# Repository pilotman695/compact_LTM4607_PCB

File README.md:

# compact_LTM4607_PCB
A compact, 98% efficient, non-isolated DC-DC converter board based around the LTM4607

Input: 4.5-36V

Output: 0.8-24V, 5A (boost mode), 10A (buck mode)

## Version 1
Stand-off mounting, solderable wire connections

## Version 2
Card-edge style, compacted

Assembly tutorial: [https://www.youtube.com/watch?v=_QmpLCoHiIg](https://www.youtube.com/watch?v=_QmpLCoHiIg)

## Carrier Board
3 card-edge connectors, hotswapping, reverse polarity protection, switchable output nodes, undervoltage/overvoltage lockout

Input: 12.5-36V

Output: 3.3-24V

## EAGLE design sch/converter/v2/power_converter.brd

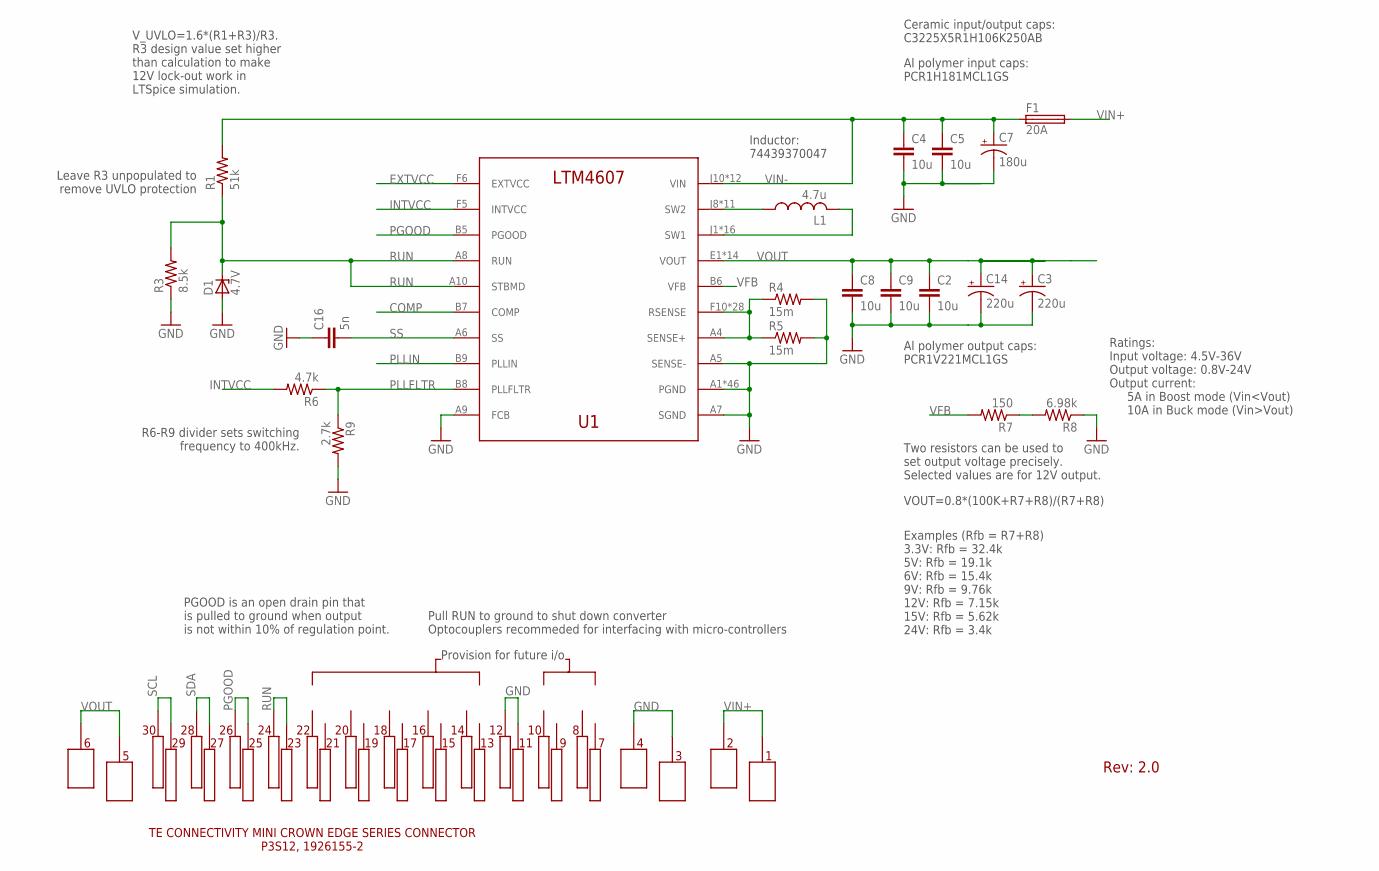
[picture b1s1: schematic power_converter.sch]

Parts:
C2, C4, C5, C8, C9: 10u; C1210
C3, C14: 220u; PCR1V221MCL1GS
C7: 180u; PCR1H181MCL1GS
C16: 5n; C0603
D1: 4.7V; SOD80C
F1: 20A; R1206
L1: 4.7u; PA4343.472ANLT
R1: 51k; R0603
R3: 8.5k; R0603
R4, R5: 15m; R1206
R6: 4.7k; R0603
R7: 150; R0603
R8: 6.98k; R0603
R9: 2.7k; R0603
U1: LTM4607EVPBF; LGA-141
U$1: 1926155-2_CARD

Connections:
COMP: U1.B7 (COMP)
EXTVCC: U1.F6 (EXTVCC)
GND: C2.2, C3.NEG (-), C4.2, C5.2, C7.NEG (-), C8.2, C9.2, C14.NEG (-), C16.1, D1.A, R3.1, R4.2, R5.2, R8.1, R9.2, U1.A1 (PGND), U1.A2 (PGND), U1.A3 (PGND), U1.A5 (SENSE-), U1.A7 (SGND), U1.A9 (FCB), U1.A11 (PGND), U1.A12 (PGND), U1.B1 (PGND), U1.B2 (PGND), U1.B3 (PGND), U1.B4 (PGND), U1.B10 (PGND), U1.B11 (PGND), U1.B12 (PGND), U1.C1 (PGND), U1.C2 (PGND), U1.C3 (PGND), U1.C4 (PGND), U1.C5 (PGND), U1.C6 (PGND), U1.C7 (PGND), U1.C8 (PGND), U1.C9 (PGND), U1.C10 (PGND), U1.C11 (PGND), U1.C12 (PGND), U1.D1 (PGND), U1.D2 (PGND), U1.D3 (PGND), U1.D4 (PGND), U1.D5 (PGND), U1.D6 (PGND), U1.D7 (PGND), U1.D8 (PGND), U1.D9 (PGND), U1.D10 (PGND), U1.D11 (PGND), U1.D12 (PGND), U1.E3 (PGND), U1.E4 (PGND), U1.E5 (PGND), U1.E6 (PGND), U1.E7 (PGND), U1.E8 (PGND), U1.E9 (PGND), U1.E10 (PGND), U1.E11 (PGND), U1.E12 (PGND), U$1.P$3, U$1.P$4, U$1.P$11, U$1.P$12
INTVCC: R6.2, U1.F5 (INTVCC)
unnamed: R7.1, R8.2
PGOOD: U1.B5 (PGOOD), U$1.P$25, U$1.P$26
PLLFLTR: R6.1, R9.1, U1.B8 (PLLFLTR)
PLLIN: U1.B9 (PLLIN)
RSENSE: R4.1, R5.1, U1.A4 (SENSE+), U1.F10 (RSENSE), U1.F11 (RSENSE), U1.F12 (RSENSE), U1.G5 (RSENSE), U1.G6 (RSENSE), U1.G7 (RSENSE), U1.G8 (RSENSE), U1.G9 (RSENSE), U1.G10 (RSENSE), U1.G11 (RSENSE), U1.G12 (RSENSE), U1.H5 (RSENSE), U1.H6 (RSENSE), U1.H7 (RSENSE), U1.H8 (RSENSE), U1.H9 (RSENSE), U1.H10 (RSENSE), U1.H11 (RSENSE), U1.H12 (RSENSE), U1.J5 (RSENSE), U1.J6 (RSENSE), U1.J7 (RSENSE), U1.K5 (RSENSE), U1.K6 (RSENSE), U1.L5 (RSENSE), U1.L6 (RSENSE), U1.M5 (RSENSE), U1.M6 (RSENSE)
RUN: D1.C, R1.1, R3.2, U1.A8 (RUN), U1.A10 (STBMD), U$1.P$23, U$1.P$24
SCL: U$1.P$29, U$1.P$30
SDA: U$1.P$27, U$1.P$28
SS: C16.2, U1.A6 (SS)
SW1: L1.P$2 (2), U1.J1 (SW1), U1.J2 (SW1), U1.J3 (SW1), U1.J4 (SW1), U1.K1 (SW1), U1.K2 (SW1), U1.K3 (SW1), U1.K4 (SW1), U1.L1 (SW1), U1.L2 (SW1), U1.L3 (SW1), U1.L4 (SW1), U1.M1 (SW1), U1.M2 (SW1), U1.M3 (SW1), U1.M4 (SW1)
SW2: L1.P$1 (1), U1.J8 (SW2), U1.J9 (SW2), U1.K7 (SW2), U1.K8 (SW2), U1.K9 (SW2), U1.L7 (SW2), U1.L8 (SW2), U1.L9 (SW2), U1.M7 (SW2), U1.M8 (SW2), U1.M9 (SW2)
VFB: R7.2, U1.B6 (VFB)
VIN+: F1.2, U$1.P$1, U$1.P$2
VIN-: C4.1, C5.1, C7.POS (+), F1.1, R1.2, U1.J10 (VIN), U1.J11 (VIN), U1.J12 (VIN), U1.K10 (VIN), U1.K11 (VIN), U1.K12 (VIN), U1.L10 (VIN), U1.L11 (VIN), U1.L12 (VIN), U1.M10 (VIN), U1.M11 (VIN), U1.M12 (VIN)
VOUT: C2.1, C3.POS (+), C8.1, C9.1, C14.POS (+), U1.E1 (VOUT), U1.E2 (VOUT), U1.F1 (VOUT), U1.F2 (VOUT), U1.F3 (VOUT), U1.F4 (VOUT), U1.G1 (VOUT), U1.G2 (VOUT), U1.G3 (VOUT), U1.G4 (VOUT), U1.H1 (VOUT), U1.H2 (VOUT), U1.H3 (VOUT), U1.H4 (VOUT), U$1.P$5, U$1.P$6

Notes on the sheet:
Ceramic input/output caps: C3225X5R1H106K250AB
Al polymer input caps: PCR1H181MCL1GS
Al polymer output caps: PCR1V221MCL1GS
Two resistors can be used to set output voltage precisely. Selected values are for 12V output.
VOUT=0.8*(100K+R7+R8)/(R7+R8)
V_UVLO=1.6*(R1+R3)/R3. R3 design value set higher than calculation to make 12V lock-out work in LTSpice simulation.
Leave R3 unpopulated to remove UVLO protection
R6-R9 divider sets switching frequency to 400kHz.
PGOOD is an open drain pin that is pulled to ground when output is not within 10% of regulation point.
Examples (Rfb = R7+R8) 3.3V: Rfb = 32.4k 5V: Rfb = 19.1k 6V: Rfb = 15.4k 9V: Rfb = 9.76k 12V: Rfb = 7.15k 15V: Rfb = 5.62k 24V: Rfb = 3.4k
Ratings: Input voltage: 4.5V-36V Output voltage: 0.8V-24V Output current: 5A in Boost mode (Vin<Vout) 10A in Buck mode (Vin>Vout)
Pull RUN to ground to shut down converter Optocouplers recommeded for interfacing with micro-controllers
Inductor: 74439370047
Rev: 2.0
Provision for future i/o

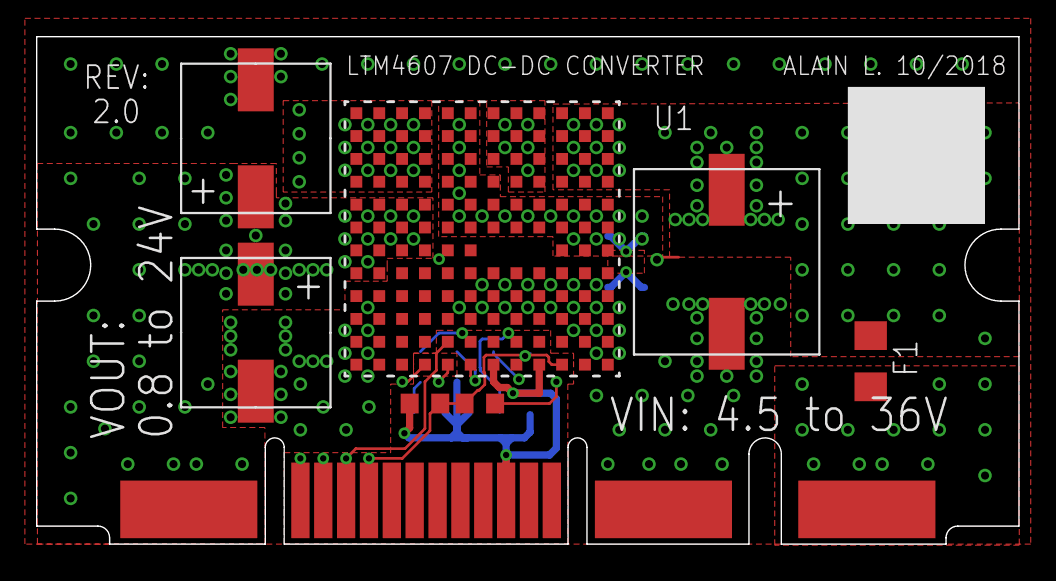
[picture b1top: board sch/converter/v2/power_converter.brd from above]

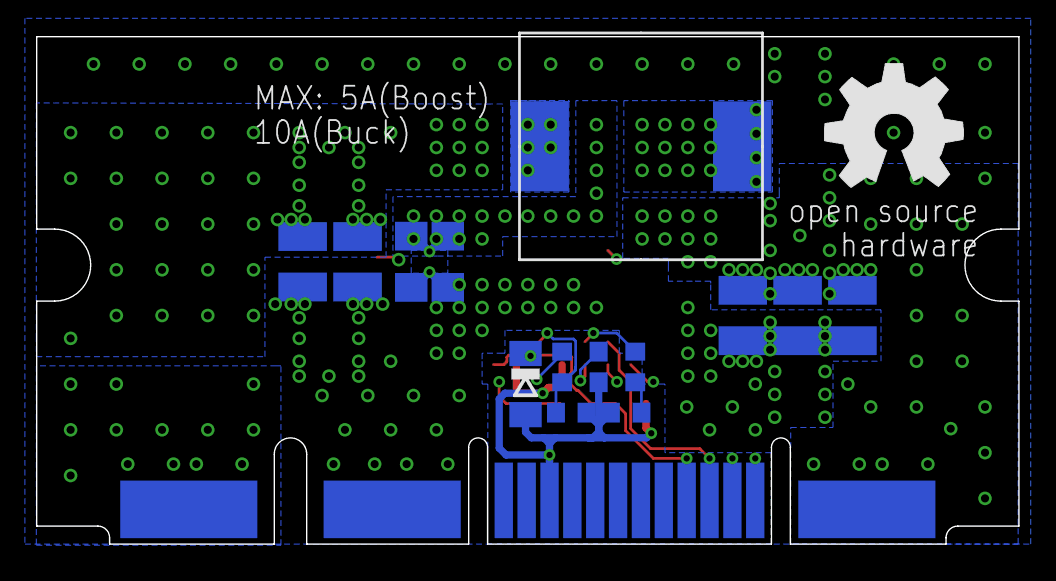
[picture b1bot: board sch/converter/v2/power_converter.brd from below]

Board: 4 copper layers, 54.6 x 28.2 mm, 24 parts (15 on the bottom side), 16 nets.

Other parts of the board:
U$2: OSHW_8MM
U$5: A4L-LOC

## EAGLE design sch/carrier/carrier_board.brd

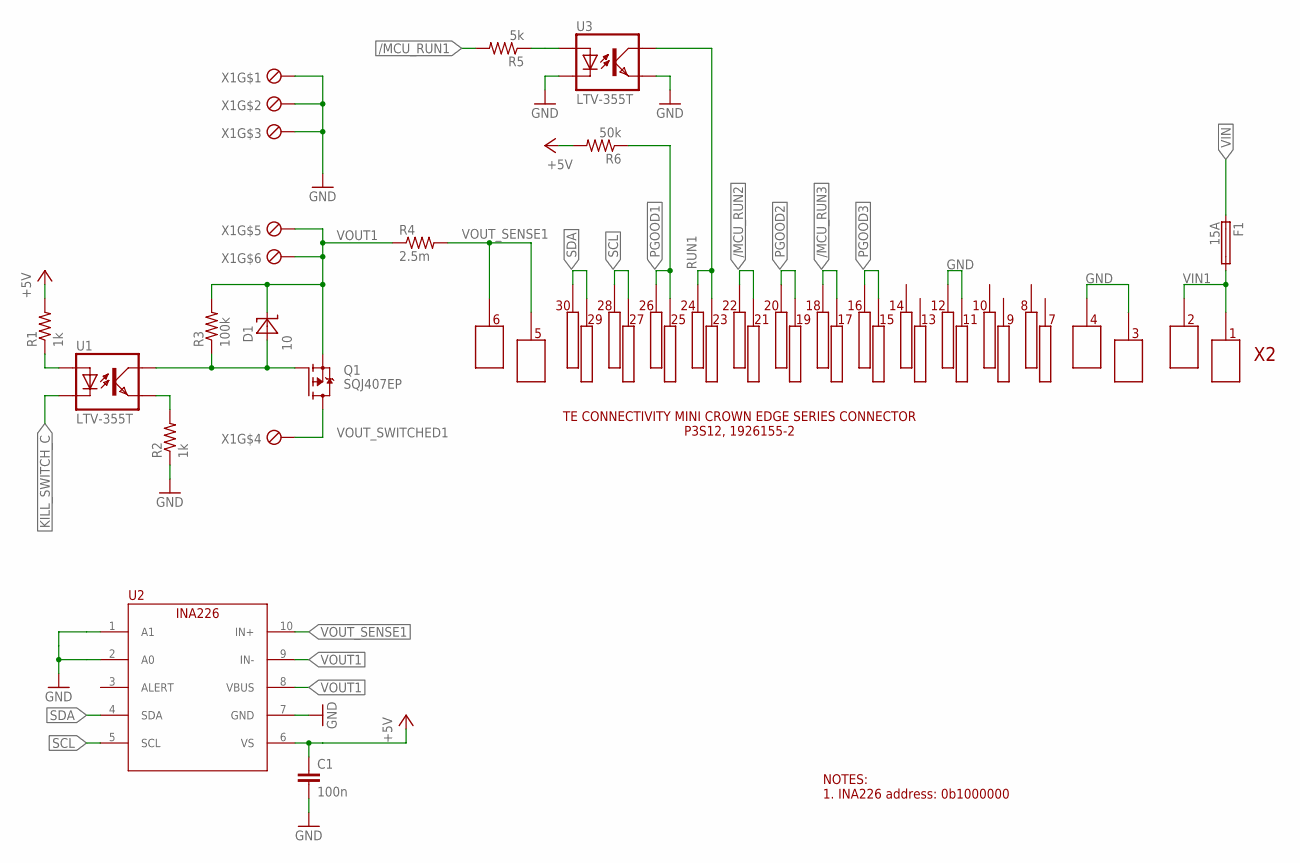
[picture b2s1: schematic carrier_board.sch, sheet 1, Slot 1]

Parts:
C1: 100n; C0603
D1: 10; SOD123
F1: 15A; 3557-10
Q1: SQJ407EP; POWERPAK_SO8L_SINGLE
R1, R2: 1k; R0603
R3: 100k; R0603
R4: 2.5m; R2512
R5: 5k; R0603
R6: 50k; R0603
U1, U3: LTV-355T; SMD4
U2: INA226; MSOP10
X1: 284391-6
X2: 1926155-2_SOCK

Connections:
+5V: C1.1, R1.2, R6.2, U2.6 (VS); also elsewhere on the board
/MCU_RUN1: R5.2; also elsewhere on the board
/MCU_RUN2: X2.P$21, X2.P$22; also elsewhere on the board
/MCU_RUN3: X2.P$17, X2.P$18; also elsewhere on the board
GATE_VOUT1: D1.2 (A), Q1.P$4 (G), R3.1, U1.COLLECTOR (COL)
GND: C1.2, R2.1, U2.1 (A1), U2.2 (A0), U2.7 (GND), U3.CATHODE (C), U3.EMITTER (EMIT), X1.P$1, X1.P$2, X1.P$3, X2.P$3_1, X2.P$3_2, X2.P$3_3, X2.P$4_1, X2.P$4_2, X2.P$4_3, X2.P$11, X2.P$12; also elsewhere on the board
KILL_SWITCH_C: U1.CATHODE (C); also elsewhere on the board
unnamed: R2.2, U1.EMITTER (EMIT)
unnamed: R5.1, U3.ANODE (A)
unnamed: R1.1, U1.ANODE (A)
PGOOD1: R6.1, X2.P$25, X2.P$26; also elsewhere on the board
PGOOD2: X2.P$19, X2.P$20; also elsewhere on the board
PGOOD3: X2.P$15, X2.P$16; also elsewhere on the board
RUN1: U3.COLLECTOR (COL), X2.P$23, X2.P$24
SCL: U2.5 (SCL), X2.P$27, X2.P$28; also elsewhere on the board
SDA: U2.4 (SDA), X2.P$29, X2.P$30; also elsewhere on the board
VIN: F1.P$1 (1), F1.P$2 (1); also elsewhere on the board
VIN1: F1.P$3 (2), F1.P$4 (2), X2.P$1_1, X2.P$1_2, X2.P$1_3, X2.P$2_1, X2.P$2_2, X2.P$2_3
VOUT1: D1.1 (C), Q1.P$1 (S), Q1.P$2 (S), Q1.P$3 (S), R3.2, R4.1, U2.8 (VBUS), U2.9 (IN-), X1.P$5, X1.P$6
VOUT_SENSE1: R4.2, U2.10 (IN+), X2.P$5_1, X2.P$5_2, X2.P$5_3, X2.P$6_1, X2.P$6_2, X2.P$6_3
VOUT_SWITCHED1: Q1.P$5 (D), Q1.P$6 (D), Q1.P$7 (D), Q1.P$8 (D), X1.P$4

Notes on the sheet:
NOTES: 1. INA226 address: 0b1000000

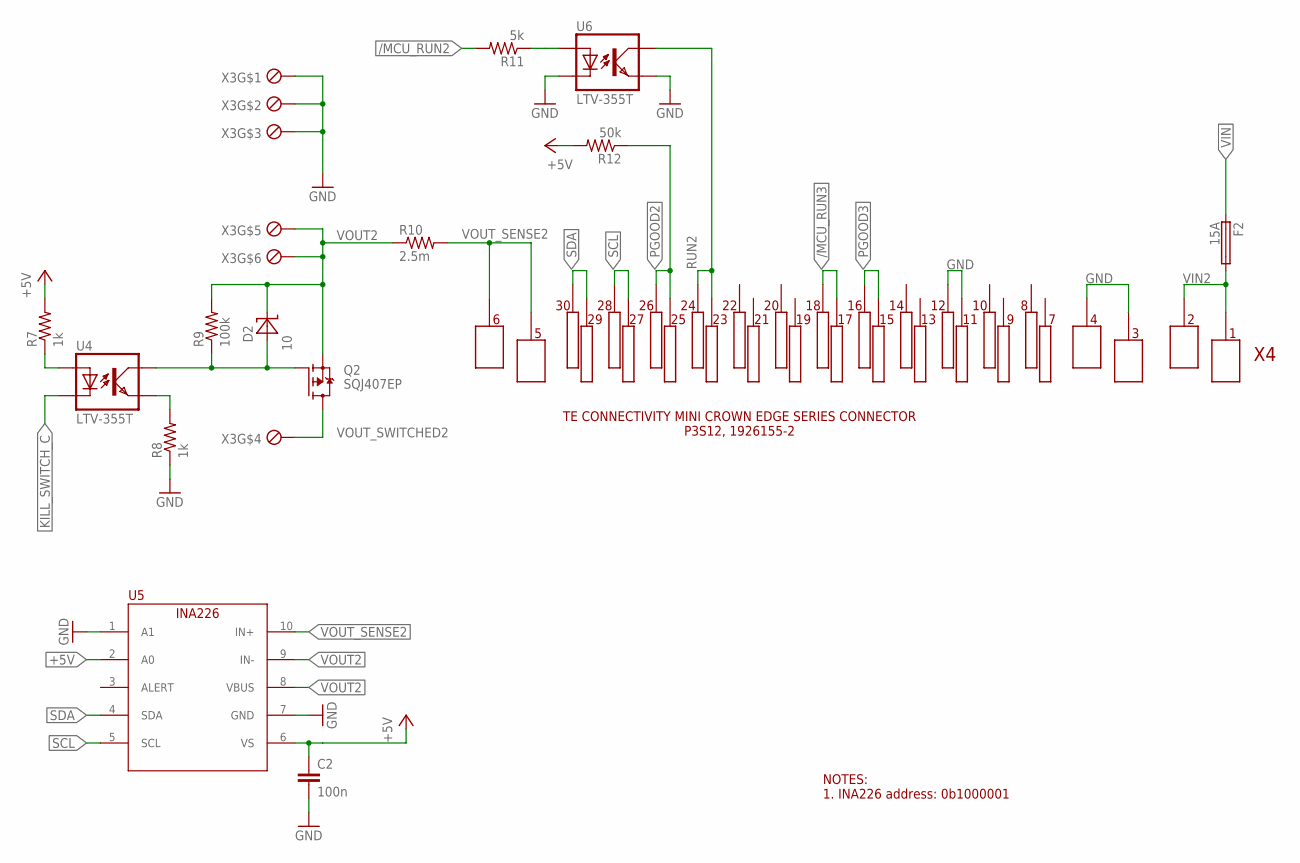
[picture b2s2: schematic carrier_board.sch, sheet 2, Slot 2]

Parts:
C2: 100n; C0603
D2: 10; SOD123
F2: 15A; 3557-10
Q2: SQJ407EP; POWERPAK_SO8L_SINGLE
R7, R8: 1k; R0603
R9: 100k; R0603
R10: 2.5m; R2512
R11: 5k; R0603
R12: 50k; R0603
U4, U6: LTV-355T; SMD4
U5: INA226; MSOP10
X3: 284391-6
X4: 1926155-2_SOCK

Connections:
+5V: C2.1, R7.2, R12.2, U5.2 (A0), U5.6 (VS); also elsewhere on the board
/MCU_RUN2: R11.2; also elsewhere on the board
/MCU_RUN3: X4.P$17, X4.P$18; also elsewhere on the board
GATE_VOUT2: D2.2 (A), Q2.P$4 (G), R9.1, U4.COLLECTOR (COL)
GND: C2.2, R8.1, U5.1 (A1), U5.7 (GND), U6.CATHODE (C), U6.EMITTER (EMIT), X3.P$1, X3.P$2, X3.P$3, X4.P$3_1, X4.P$3_2, X4.P$3_3, X4.P$4_1, X4.P$4_2, X4.P$4_3, X4.P$11, X4.P$12; also elsewhere on the board
KILL_SWITCH_C: U4.CATHODE (C); also elsewhere on the board
unnamed: R8.2, U4.EMITTER (EMIT)
unnamed: R7.1, U4.ANODE (A)
unnamed: R11.1, U6.ANODE (A)
PGOOD2: R12.1, X4.P$25, X4.P$26; also elsewhere on the board
PGOOD3: X4.P$15, X4.P$16; also elsewhere on the board
RUN2: U6.COLLECTOR (COL), X4.P$23, X4.P$24
SCL: U5.5 (SCL), X4.P$27, X4.P$28; also elsewhere on the board
SDA: U5.4 (SDA), X4.P$29, X4.P$30; also elsewhere on the board
VIN: F2.P$1 (1), F2.P$2 (1); also elsewhere on the board
VIN2: F2.P$3 (2), F2.P$4 (2), X4.P$1_1, X4.P$1_2, X4.P$1_3, X4.P$2_1, X4.P$2_2, X4.P$2_3
VOUT2: D2.1 (C), Q2.P$1 (S), Q2.P$2 (S), Q2.P$3 (S), R9.2, R10.1, U5.8 (VBUS), U5.9 (IN-), X3.P$5, X3.P$6
VOUT_SENSE2: R10.2, U5.10 (IN+), X4.P$5_1, X4.P$5_2, X4.P$5_3, X4.P$6_1, X4.P$6_2, X4.P$6_3
VOUT_SWITCHED2: Q2.P$5 (D), Q2.P$6 (D), Q2.P$7 (D), Q2.P$8 (D), X3.P$4

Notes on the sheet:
NOTES: 1. INA226 address: 0b1000001

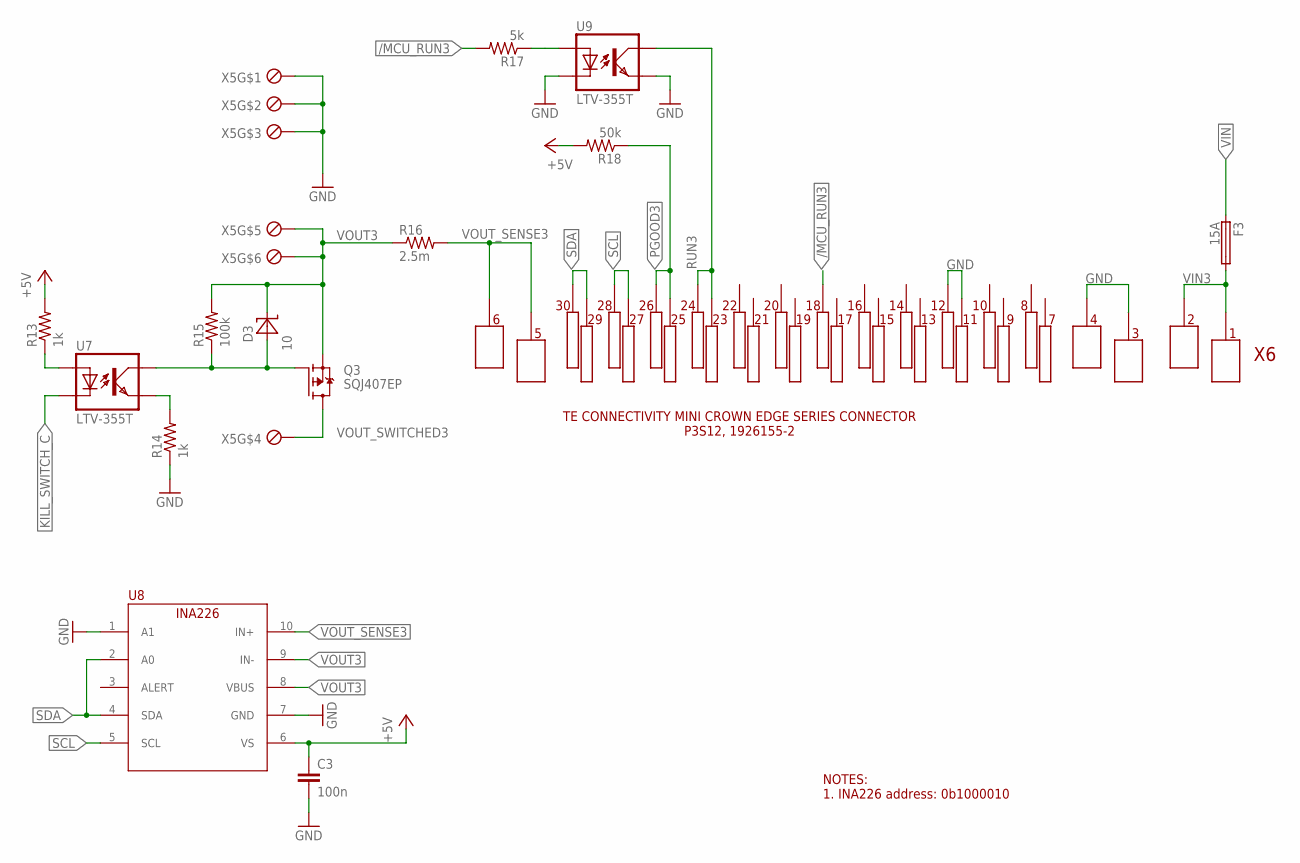
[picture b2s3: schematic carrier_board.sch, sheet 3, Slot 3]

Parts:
C3: 100n; C0603
D3: 10; SOD123
F3: 15A; 3557-10
Q3: SQJ407EP; POWERPAK_SO8L_SINGLE
R13, R14: 1k; R0603
R15: 100k; R0603
R16: 2.5m; R2512
R17: 5k; R0603
R18: 50k; R0603
U7, U9: LTV-355T; SMD4
U8: INA226; MSOP10
X5: 284391-6
X6: 1926155-2_SOCK

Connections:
+5V: C3.1, R13.2, R18.2, U8.6 (VS); also elsewhere on the board
/MCU_RUN3: R17.2, X6.P$18; also elsewhere on the board
GATE_VOUT3: D3.2 (A), Q3.P$4 (G), R15.1, U7.COLLECTOR (COL)
GND: C3.2, R14.1, U8.1 (A1), U8.7 (GND), U9.CATHODE (C), U9.EMITTER (EMIT), X5.P$1, X5.P$2, X5.P$3, X6.P$3_1, X6.P$3_2, X6.P$3_3, X6.P$4_1, X6.P$4_2, X6.P$4_3, X6.P$11, X6.P$12; also elsewhere on the board
KILL_SWITCH_C: U7.CATHODE (C); also elsewhere on the board
unnamed: R14.2, U7.EMITTER (EMIT)
unnamed: R13.1, U7.ANODE (A)
unnamed: R17.1, U9.ANODE (A)
PGOOD3: R18.1, X6.P$25, X6.P$26; also elsewhere on the board
RUN3: U9.COLLECTOR (COL), X6.P$23, X6.P$24
SCL: U8.5 (SCL), X6.P$27, X6.P$28; also elsewhere on the board
SDA: U8.2 (A0), U8.4 (SDA), X6.P$29, X6.P$30; also elsewhere on the board
VIN: F3.P$1 (1), F3.P$2 (1); also elsewhere on the board
VIN3: F3.P$3 (2), F3.P$4 (2), X6.P$1_1, X6.P$1_2, X6.P$1_3, X6.P$2_1, X6.P$2_2, X6.P$2_3
VOUT3: D3.1 (C), Q3.P$1 (S), Q3.P$2 (S), Q3.P$3 (S), R15.2, R16.1, U8.8 (VBUS), U8.9 (IN-), X5.P$5, X5.P$6
VOUT_SENSE3: R16.2, U8.10 (IN+), X6.P$5_1, X6.P$5_2, X6.P$5_3, X6.P$6_1, X6.P$6_2, X6.P$6_3
VOUT_SWITCHED3: Q3.P$5 (D), Q3.P$6 (D), Q3.P$7 (D), Q3.P$8 (D), X5.P$4

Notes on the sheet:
NOTES: 1. INA226 address: 0b1000010

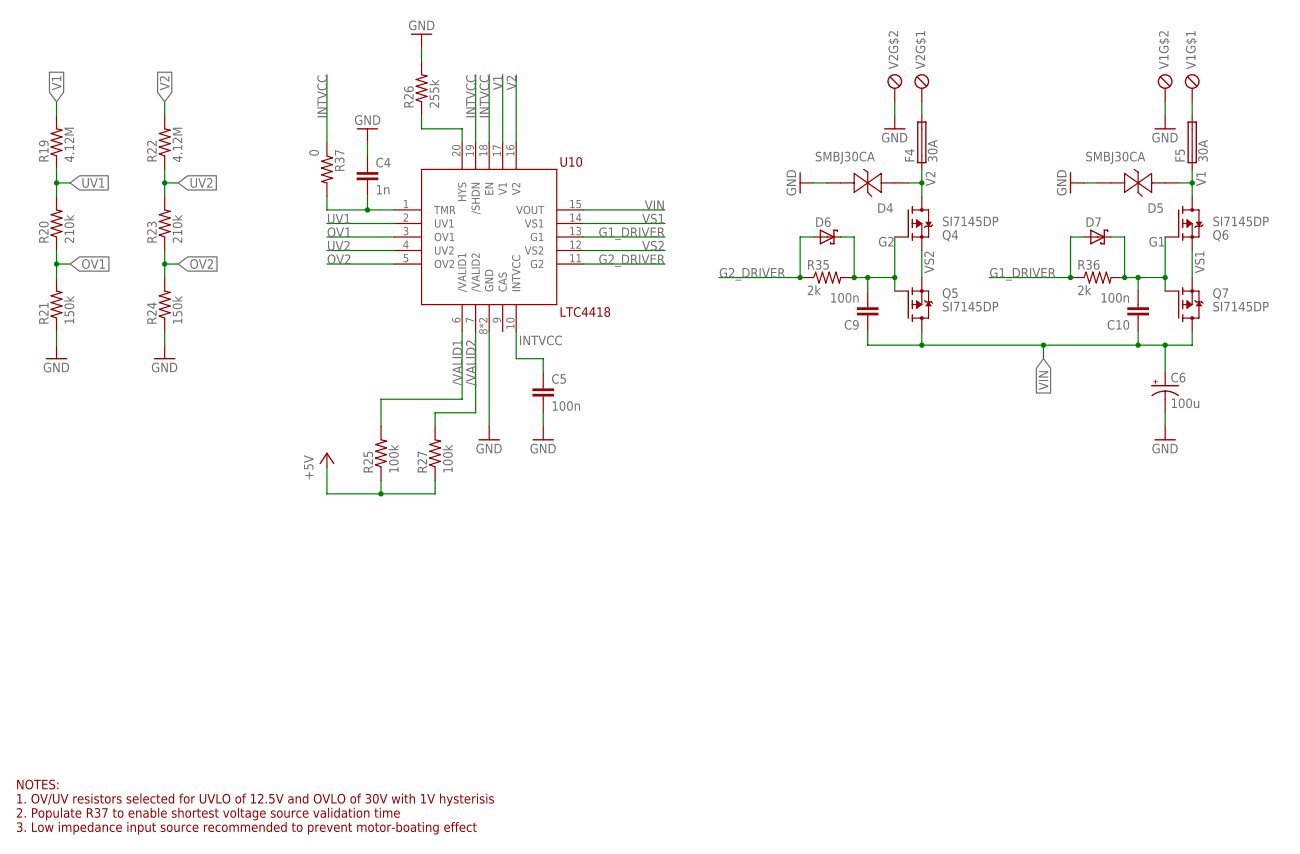
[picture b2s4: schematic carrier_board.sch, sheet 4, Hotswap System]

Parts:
C4: 1n; C0402
C5: 100n; C0402
C6: 100u; E5-10,5
C9, C10: 100n; C0603
D4, D5: SMBJ30CA; DO214AA
D6, D7: SD0603S040S0R2; CHIPLED_0603
F4, F5: 30A; 3557-10
Q4, Q5, Q6, Q7: SI7145DP; SO-8-POWERPAK
R19, R22: 4.12M; R0402
R20, R23: 210k; R0402
R21, R24: 150k; R0402
R25, R27: 100k; R0603
R26: 255k; R0402
R35, R36: 2k; R0603
R37: 0; R0402
U10: LTC4418; QFN20
V1, V2: MKDSD_1730502

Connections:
+5V: R25.1, R27.1; also elsewhere on the board
/VALID1: R25.2, U10.6 (/VALID1); also elsewhere on the board
/VALID2: R27.2, U10.7 (/VALID2); also elsewhere on the board
G1: C10.2, D7.C, Q6.4 (G), Q7.4 (G), R36.2
G1_DRIVER: D7.A, R36.1, U10.13 (G1)
G2: C9.2, D6.C, Q4.4 (G), Q5.4 (G), R35.2
G2_DRIVER: D6.A, R35.1, U10.11 (G2)
GND: C4.1, C5.2, C6.-, D4.A (2), D5.A (2), R21.1, R24.1, R26.2, U10.8 (GND), U10.EXP (GND), V1.P$2, V1.P$4, V2.P$2, V2.P$4; also elsewhere on the board
HYS: R26.1, U10.20 (HYS)
INTVCC: C5.1, R37.1, U10.10 (INTVCC), U10.18 (EN), U10.19 (/SHDN)
OV1: R20.1, R21.2, U10.3 (OV1)
OV2: R23.1, R24.2, U10.5 (OV2)
TMR: C4.2, R37.2, U10.1 (TMR)
UV1: R19.1, R20.2, U10.2 (UV1)
UV2: R22.1, R23.2, U10.4 (UV2)
V1: D5.C (1), F5.P$1 (1), F5.P$2 (1), Q6.5 (D), Q6.6 (D), Q6.7 (D), Q6.8 (D), Q6.P$1 (D), R19.2, U10.17 (V1)
V2: D4.C (1), F4.P$1 (1), F4.P$2 (1), Q4.5 (D), Q4.6 (D), Q4.7 (D), Q4.8 (D), Q4.P$1 (D), R22.2, U10.16 (V2)
VBAT1: F5.P$3 (2), F5.P$4 (2), V1.P$1, V1.P$3
VBAT2: F4.P$3 (2), F4.P$4 (2), V2.P$1, V2.P$3
VIN: C6.+, C9.1, C10.1, Q5.5 (D), Q5.6 (D), Q5.7 (D), Q5.8 (D), Q5.P$1 (D), Q7.5 (D), Q7.6 (D), Q7.7 (D), Q7.8 (D), Q7.P$1 (D), U10.15 (VOUT); also elsewhere on the board
VS1: Q6.1 (S), Q6.2 (S), Q6.3 (S), Q7.1 (S), Q7.2 (S), Q7.3 (S), U10.14 (VS1)
VS2: Q4.1 (S), Q4.2 (S), Q4.3 (S), Q5.1 (S), Q5.2 (S), Q5.3 (S), U10.12 (VS2)

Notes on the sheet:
NOTES: 1. OV/UV resistors selected for UVLO of 12.5V and OVLO of 30V with 1V hysterisis 2. Populate R37 to enable shortest voltage source validation time 3. Low impedance input source recommended to prevent motor-boating effect

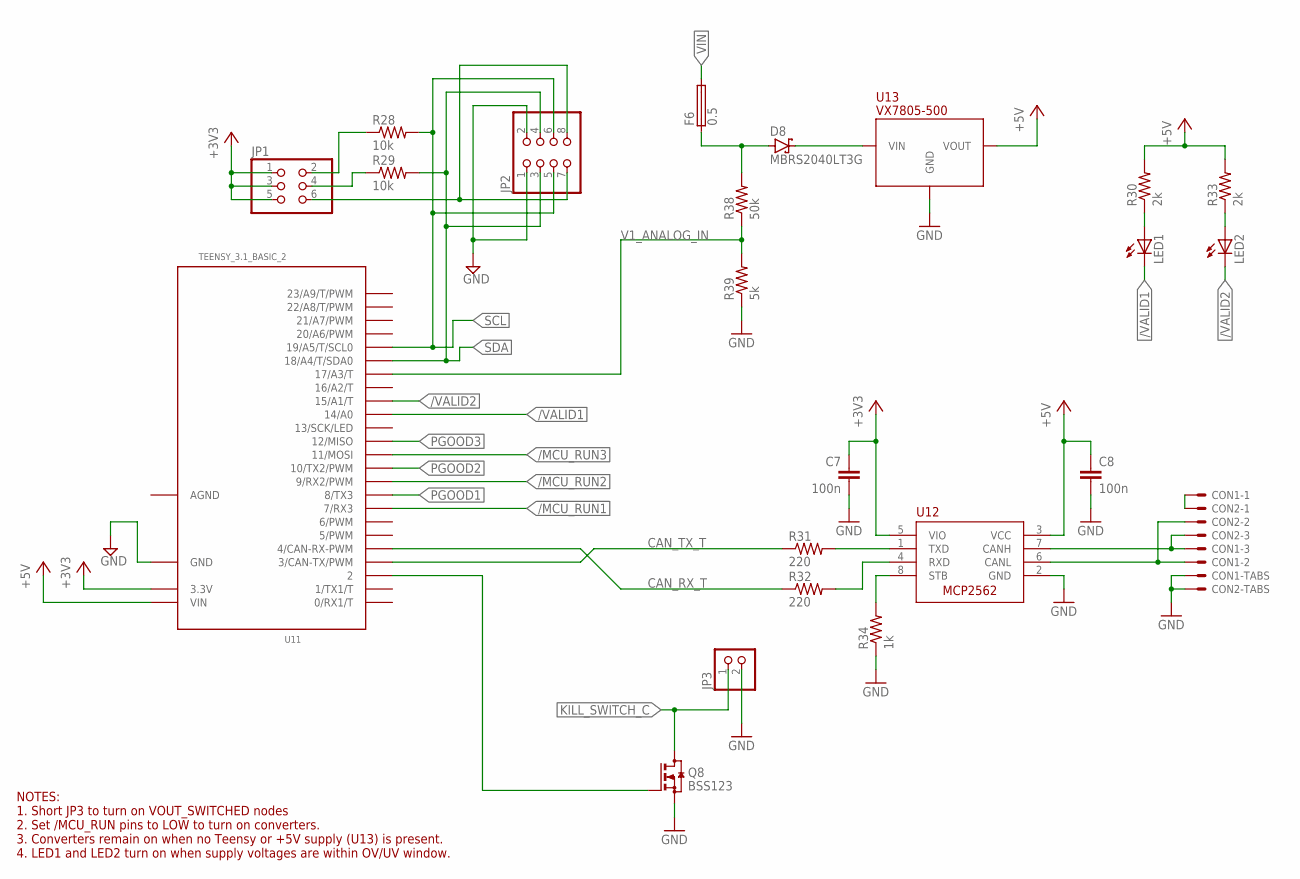
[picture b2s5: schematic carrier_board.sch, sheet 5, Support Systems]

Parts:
C7, C8: 100n; C0805
CON1, CON2: SM03B-GHS-TB
D8: MBRS2040LT3G; SMB
F6: 0.5; R1206
JP1: PINHD-2X3; 2X03
JP2: PINHD-2X4; 2X04
JP3: PINHD-1X02_2.54-SMD-90°; 1X02SMD/90
LED1, LED2: LEDCHIPLED_0603; CHIPLED_0603
Q8: BSS123; SOT23
R28, R29: 10k; R0805
R30, R33: 2k; R0603
R31, R32: 220; R0805
R34: 1k; R0805
R38: 50k; R0603
R39: 5k; R0603
U11: TEENSY_3.1_BASIC_2
U12: MCP2562; SO-8
U13: VX7805-500; 0.1"_LINEAR_REGULATOR_REPLACEMENT

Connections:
+3V3: C7.1, JP1.1, JP1.3, JP1.5, U11.3.3V, U12.5 (VIO)
+5V: C8.1, R30.2, R33.2, U11.VIN, U12.3 (VCC), U13.3 (VOUT); also elsewhere on the board
/MCU_RUN1: U11.7 (7/RX3); also elsewhere on the board
/MCU_RUN2: U11.9 (9/RX2/PWM); also elsewhere on the board
/MCU_RUN3: U11.11 (11/MOSI); also elsewhere on the board
/VALID1: LED1.C, U11.14/A0; also elsewhere on the board
/VALID2: LED2.C, U11.15/A1 (15/A1/T); also elsewhere on the board
AGND: U11.AGND
CANH: CON1.P$3, CON2.P$3, U12.7 (CANH)
CANL: CON1.P$2, CON2.P$2, U12.6 (CANL)
CANSH: CON1.P$1, CON2.P$1
CAN_RX: R32.2, U12.4 (RXD)
CAN_RX_T: R32.1, U11.4 (4/CAN-RX-PWM)
CAN_TX: R31.2, U12.1 (TXD)
CAN_TX_T: R31.1, U11.3 (3/CAN-TX/PWM)
GND: C7.2, C8.2, CON1.P$4, CON1.P$5, CON2.P$4, CON2.P$5, JP2.1, JP2.2, JP3.2, Q8.2 (S), R34.1, R39.1, U11.GND, U12.2 (GND), U13.2 (GND); also elsewhere on the board
I2C_3V3: JP1.6, JP2.7, JP2.8
KILL_SWITCH_C: JP3.1, Q8.3 (D); also elsewhere on the board
unnamed: D8.A, F6.1, R38.2
unnamed: LED1.A, R30.1
unnamed: LED2.A, R33.1
unnamed: Q8.1 (G), U11.2
unnamed: D8.C, U13.1 (VIN)
PGOOD1: U11.8 (8/TX3); also elsewhere on the board
PGOOD2: U11.10 (10/TX2/PWM); also elsewhere on the board
PGOOD3: U11.12 (12/MISO); also elsewhere on the board
SCL: JP2.5, JP2.6, R28.2, U11.19/A5 (19/A5/T/SCL0); also elsewhere on the board
SCL_3V3: JP1.2, R28.1
SDA: JP2.3, JP2.4, R29.2, U11.18/A4 (18/A4/T/SDA0); also elsewhere on the board
SDA_3V3: JP1.4, R29.1
STB: R34.2, U12.8 (STB)
V1_ANALOG_IN: R38.1, R39.2, U11.17/A3 (17/A3/T)
VIN: F6.2; also elsewhere on the board

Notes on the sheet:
NOTES: 1. Short JP3 to turn on VOUT_SWITCHED nodes 2. Set /MCU_RUN pins to LOW to turn on converters. 3. Converters remain on when no Teensy or +5V supply (U13) is present. 4. LED1 and LED2 turn on when supply voltages are within OV/UV window.

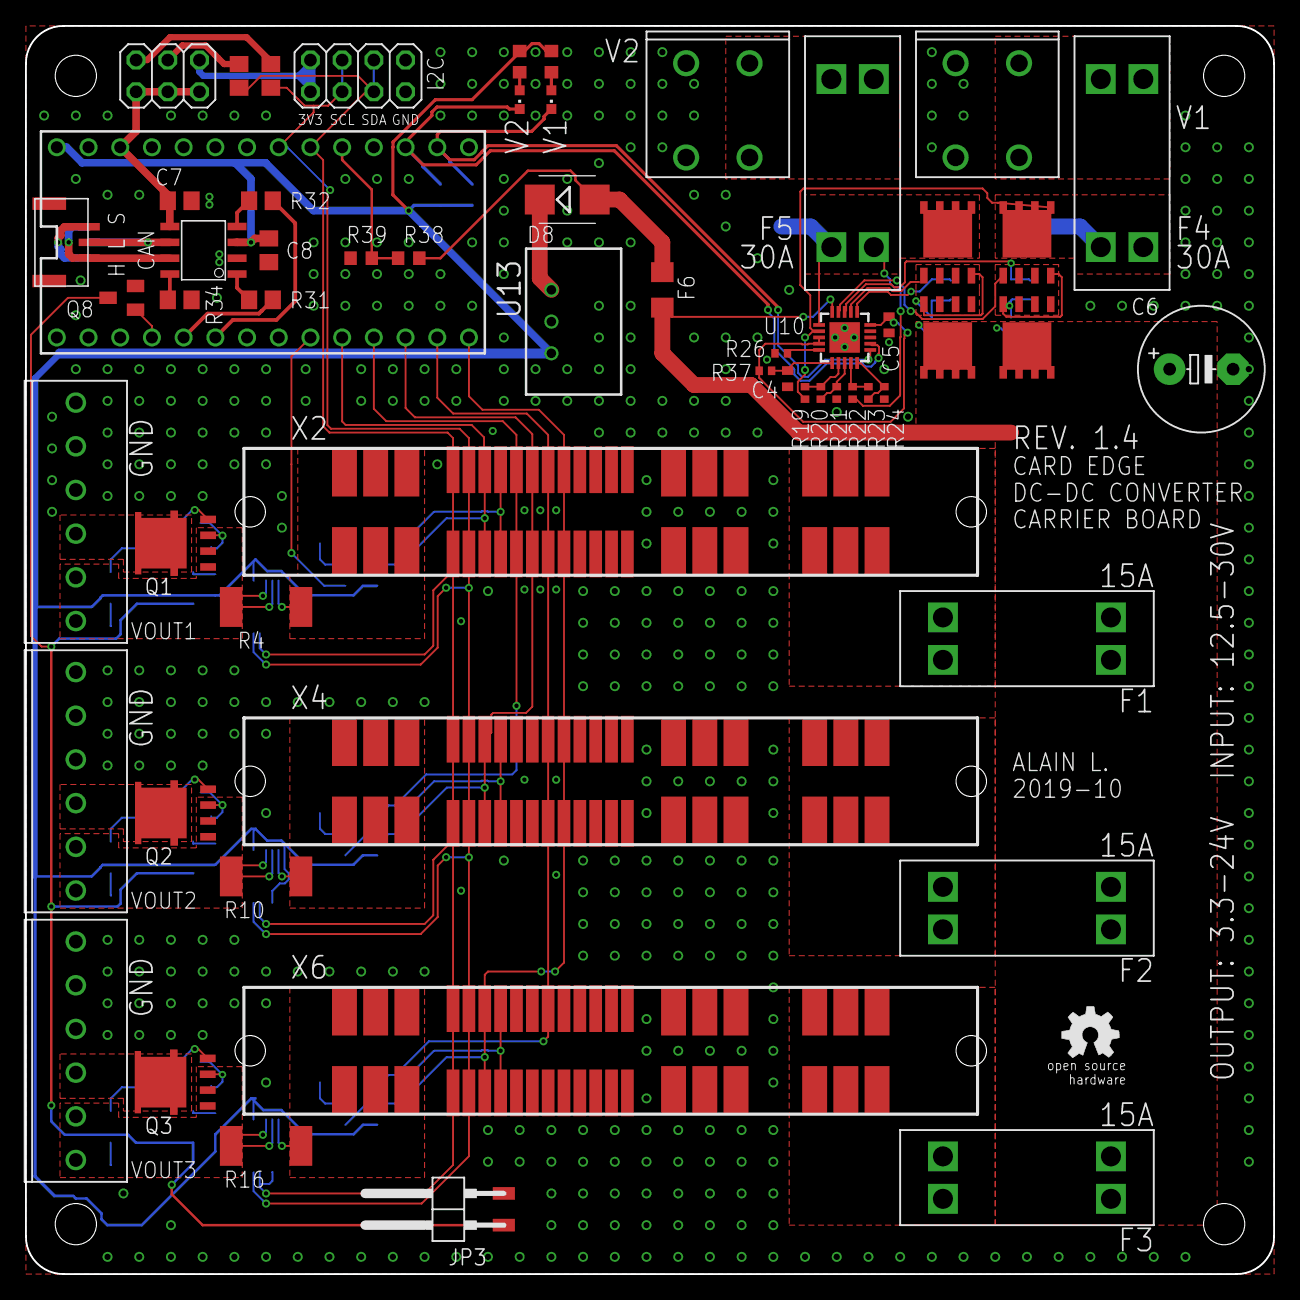
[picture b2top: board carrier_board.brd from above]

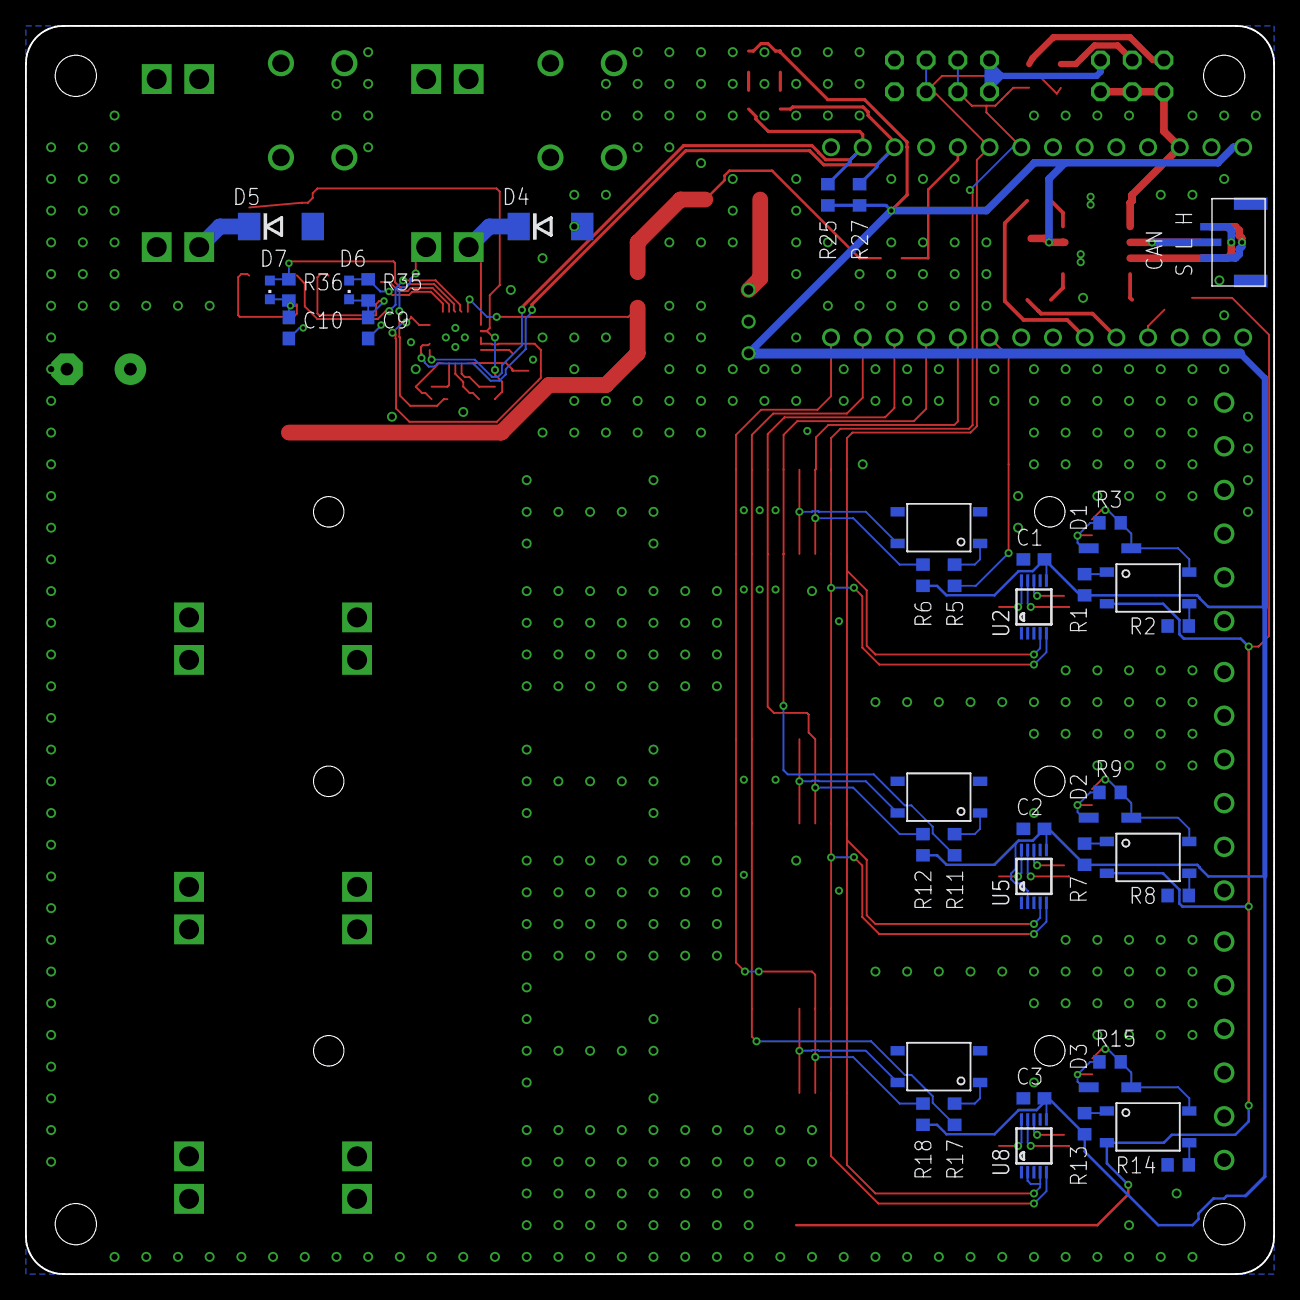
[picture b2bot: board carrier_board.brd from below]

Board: 2 copper layers, 100.0 x 100.0 mm, 105 parts (41 on the bottom side), 76 nets.

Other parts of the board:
U$1, U$2, U$3, U$4: STAND-OFF
U$5: A4L-LOC
U$7: OSHW_5MM

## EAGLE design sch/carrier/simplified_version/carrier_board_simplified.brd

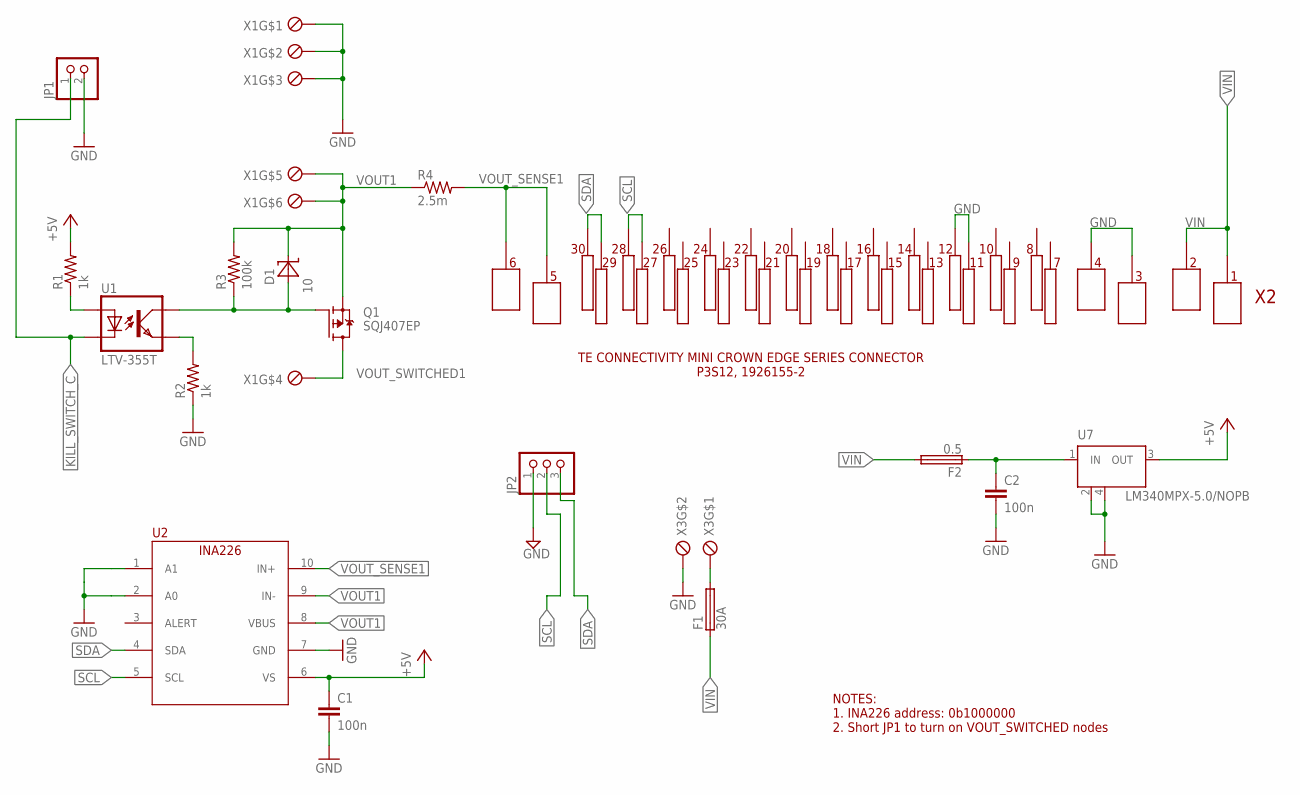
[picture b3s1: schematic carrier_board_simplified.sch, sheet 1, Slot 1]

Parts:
C1, C2: 100n; C0603
D1: 10; SOD123
F1: 30A; 3557-10
F2: 0.5; R1206
JP1: PINHD-1X02_2.54-SMD-90°; 1X02SMD/90
JP2: PINHD-1X03_2.54-SMD-90°; 1X03SMD/90
Q1: SQJ407EP; POWERPAK_SO8L_SINGLE
R1, R2: 1k; R0603
R3: 100k; R0603
R4: 2.5m; R2512
U1: LTV-355T; SMD4
U2: INA226; MSOP10
U7: LM340MPX-5.0/NOPB; SOT223
X1: 284391-6
X2: 1926155-2_SOCK
X3: OSTT7020150

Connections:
+5V: C1.1, R1.2, U2.6 (VS), U7.3 (OUT); also elsewhere on the board
GATE_VOUT1: D1.2 (A), Q1.P$4 (G), R3.1, U1.COLLECTOR (COL)
GND: C1.2, C2.2, JP1.2, JP2.1, R2.1, U2.1 (A1), U2.2 (A0), U2.7 (GND), U7.2 (GND), U7.4 (GND), X1.P$1, X1.P$2, X1.P$3, X2.P$3_1, X2.P$3_2, X2.P$3_3, X2.P$4_1, X2.P$4_2, X2.P$4_3, X2.P$11, X2.P$12, X3.2; also elsewhere on the board
KILL_SWITCH_C: JP1.1, U1.CATHODE (C); also elsewhere on the board
unnamed: C2.1, F2.1, U7.1 (IN)
unnamed: R2.2, U1.EMITTER (EMIT)
unnamed: R1.1, U1.ANODE (A)
SCL: JP2.2, U2.5 (SCL), X2.P$27, X2.P$28; also elsewhere on the board
SDA: JP2.3, U2.4 (SDA), X2.P$29, X2.P$30; also elsewhere on the board
VBAT1: F1.P$3 (2), F1.P$4 (2), X3.1
VIN: F1.P$1 (1), F1.P$2 (1), F2.2, X2.P$1_1, X2.P$1_2, X2.P$1_3, X2.P$2_1, X2.P$2_2, X2.P$2_3; also elsewhere on the board
VOUT1: D1.1 (C), Q1.P$1 (S), Q1.P$2 (S), Q1.P$3 (S), R3.2, R4.1, U2.8 (VBUS), U2.9 (IN-), X1.P$5, X1.P$6
VOUT_SENSE1: R4.2, U2.10 (IN+), X2.P$5_1, X2.P$5_2, X2.P$5_3, X2.P$6_1, X2.P$6_2, X2.P$6_3
VOUT_SWITCHED1: Q1.P$5 (D), Q1.P$6 (D), Q1.P$7 (D), Q1.P$8 (D), X1.P$4

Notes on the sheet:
NOTES: 1. INA226 address: 0b1000000 2. Short JP1 to turn on VOUT_SWITCHED nodes
